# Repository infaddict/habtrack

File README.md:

# habtrack
High Altitude Balloon Tracker 

Written by: infaddict

Project start date: February 2015

Description: Tracking software for High Altitude Ballooning.  Includes GPS location/altitude, internal & external temperature, voltage monitor, Radio transmission and optional data logging to SD card.  

Hardware: Arduino Mini Pro 3.3V 8Mhz, uBlox M8C GPS with chip antenna, Radiometrix NTX2B-FA, 2 x DS18B20 temperature sensors, microSD breakout board (SPI), various resistors

For more information visit the UK High Altitude Society here: http://ukhas.org.uk/

Also join us on IRC: irc://irc.freenode.net/highaltitude

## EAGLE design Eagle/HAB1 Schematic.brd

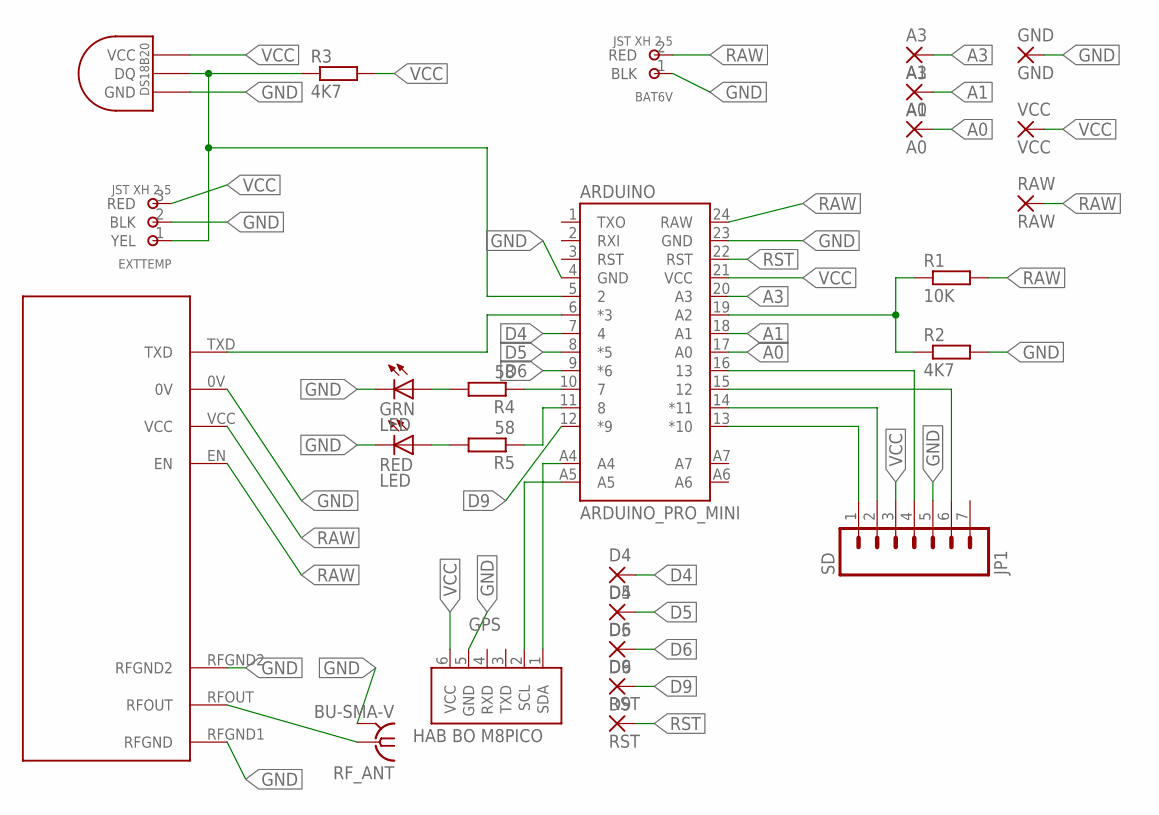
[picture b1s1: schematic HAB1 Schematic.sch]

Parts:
A0: A0; 1,6/0,8
A1: A1; 1,6/0,8
A3: A3; 1,6/0,8
ARDUINO: ARDUINO_PRO_MINI
BAT6V: JST-XH-2.5-2PIN-MAIL; JST-XH-2.5-2PIN-MAILE
D4: D4; 1,6/0,8
D5: D5; 1,6/0,8
D6: D6; 1,6/0,8
D9: D9; 1,6/0,8
EXTTEMP: JST-XH-2.5-2PIN-MAIL; JST-XH-2.5-2PIN-MAILE
GND: GND; 1,6/0,8
GPS: HAB-BO-M8PICONORMAL; HAB-BO-M8PICO
GRN: LED; LED3MM
INT: DS1820TO92; DS1820
JP1: SD; 1X07
R1: 10K; 0204/5
R2, R3: 4K7; 0204/5
R4, R5: 58; 0204/5
RAW: RAW; 1,6/0,8
RED: LED; LED3MM
RF_ANT: BU-SMA-V
RST: RST; 1,6/0,8
U$3: NTX2-VERTICAL
VCC: VCC; 1,6/0,8

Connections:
A0: A0.1, ARDUINO.17 (A0)
A1: A1.1, ARDUINO.18 (A1)
A2: ARDUINO.19 (A2), R1.1, R2.1
A3: A3.1, ARDUINO.20 (A3)
D2: ARDUINO.5 (2), EXTTEMP.1 (YEL), INT.DQ, R3.1
D4: ARDUINO.7 (4), D4.1
D5: ARDUINO.8 (*5), D5.1
D6: ARDUINO.9 (*6), D6.1
D9: ARDUINO.12 (*9), D9.1
GND: ARDUINO.4 (GND), ARDUINO.23 (GND), BAT6V.1 (BLK), EXTTEMP.2 (BLK), GND.1, GPS.5 (GND), GRN.K (C), INT.GND, JP1.5, R2.2, RED.K (C), RF_ANT.2, RF_ANT.3 (2), RF_ANT.4 (2), RF_ANT.5 (2), U$3.0V, U$3.RFGND1 (RFGND), U$3.RFGND2
unnamed: ARDUINO.13 (*10), JP1.1
unnamed: ARDUINO.10 (7), R4.1
unnamed: GRN.A, R4.2
unnamed: ARDUINO.11 (8), R5.1
unnamed: R5.2, RED.A
unnamed: ARDUINO.6 (*3), U$3.TXD
unnamed: ARDUINO.A5, GPS.2 (SCL)
unnamed: ARDUINO.15 (12), JP1.6
unnamed: ARDUINO.14 (*11), JP1.2
unnamed: ARDUINO.16 (13), JP1.4
unnamed: ARDUINO.A4, GPS.1 (SDA)
RAW: ARDUINO.24 (RAW), BAT6V.2 (RED), R1.2, RAW.1, U$3.EN, U$3.VCC
RFSIGNAL: RF_ANT.1, U$3.RFOUT
RST: ARDUINO.22 (RST), RST.1
VCC: ARDUINO.21 (VCC), EXTTEMP.3 (RED), GPS.6 (VCC), INT.VDD (VCC), JP1.3, R3.2, VCC.1

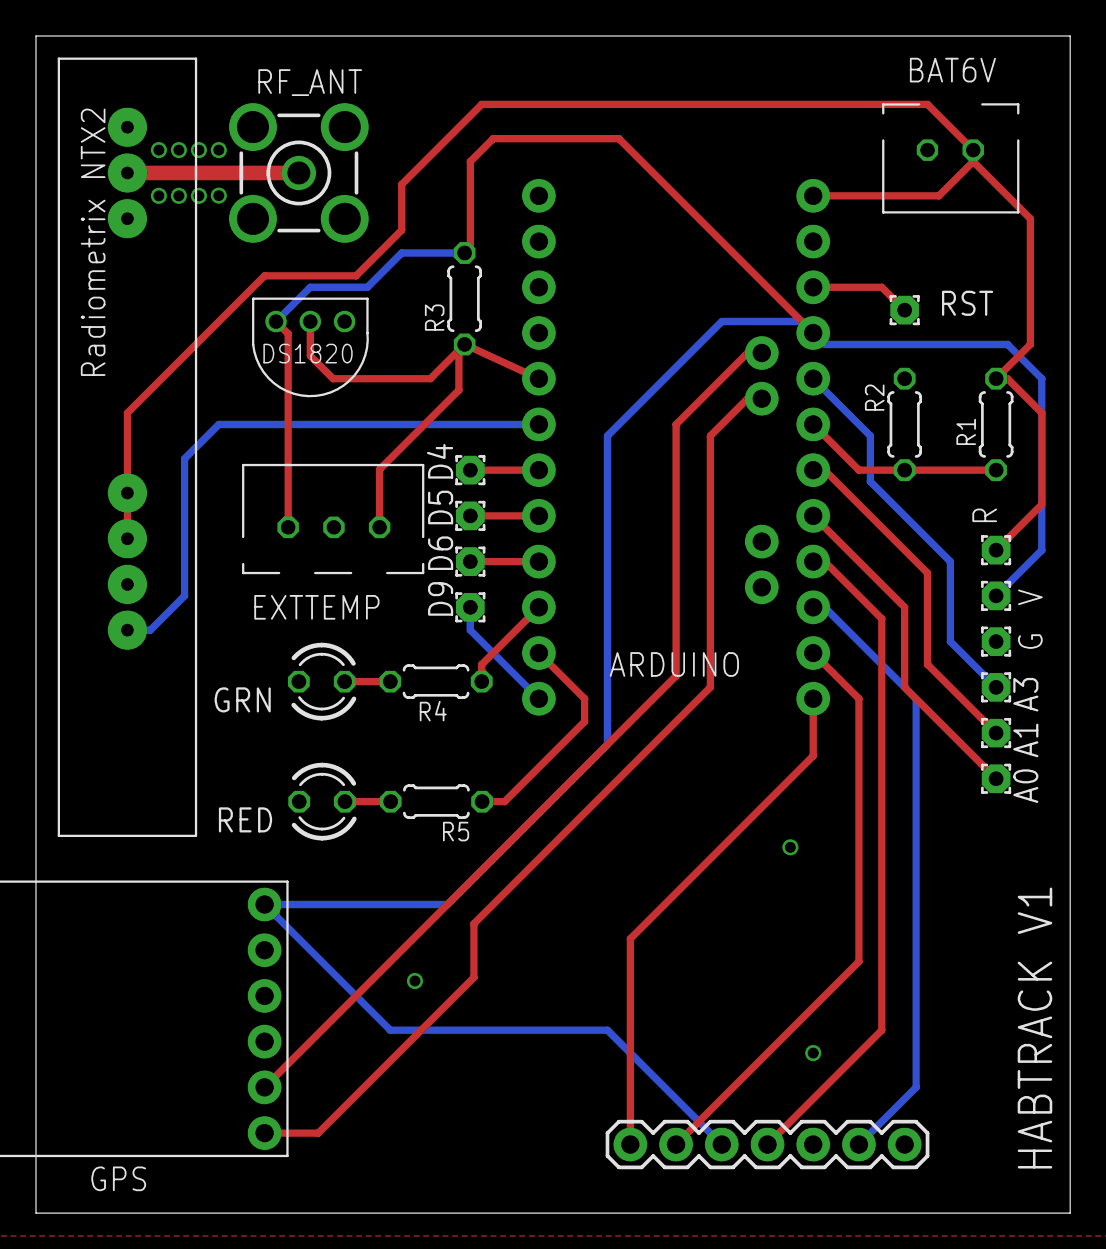
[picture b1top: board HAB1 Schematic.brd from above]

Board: 2 copper layers, 57.5 x 65.4 mm, 26 parts (0 on the bottom side), 25 nets.

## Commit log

2015-02-19 Update README.md
    Added project details
2015-02-21 Initial version
2015-02-23 General update
2015-02-26 v1 rev 0.1
2015-03-05 More v1 testing and minor changes
2015-03-05 Add Eagle files & datasheets
2015-03-10 Bug fixes
2015-04-18 Add airborne mode every 3 mins
2015-05-30 Updated PCB

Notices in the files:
parts and their libraries:
SparkFun-Boards: Licensing: Creative Commons ShareAlike 4.0 International - https://creativecommons.org/licenses/by-sa/4.0
